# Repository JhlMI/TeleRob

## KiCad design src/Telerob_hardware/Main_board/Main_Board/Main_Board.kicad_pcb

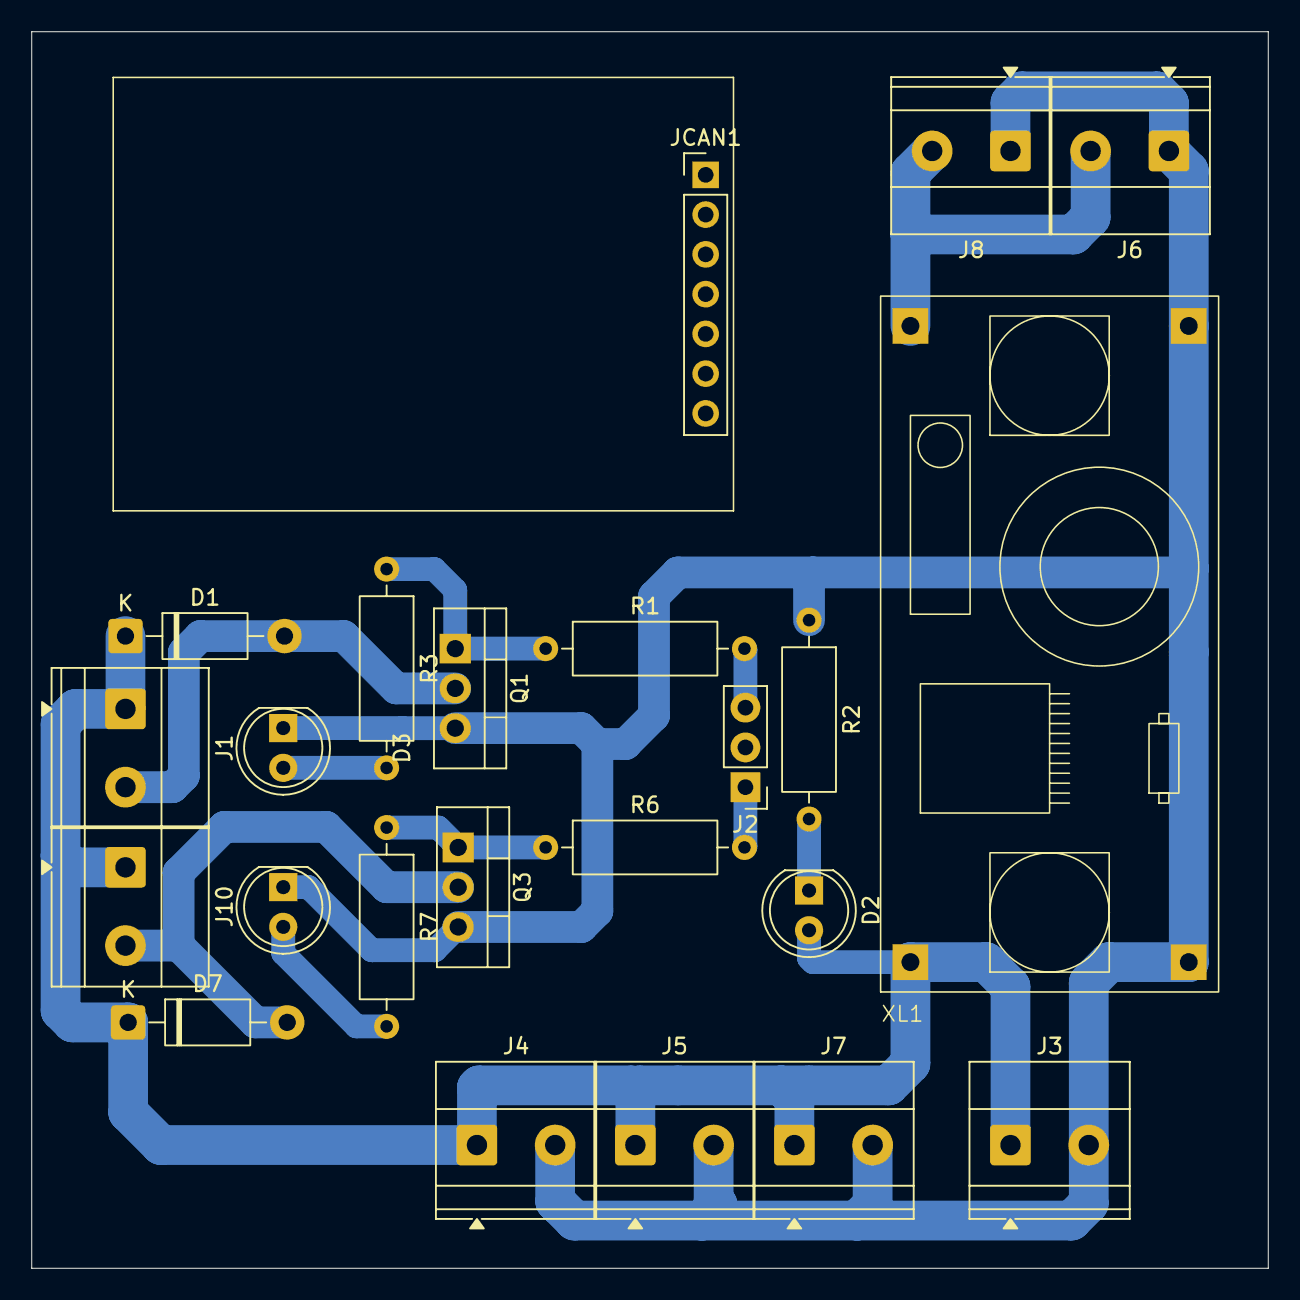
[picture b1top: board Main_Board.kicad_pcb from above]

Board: 2 copper layers, 79.0 x 79.0 mm, 23 parts (0 on the bottom side), 12 nets.

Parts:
D1, D7: 1N4007; D_DO-41_SOD81_P10.16mm_Horizontal
D2, D3, D6: LED; LED_D5.0mm
J1, J10: Mosfet; TerminalBlock_Phoenix_MKDS-1,5-2_1x02_P5.00mm_Horizontal
J2: Conn_01x03; PinHeader_1x03_P2.54mm_Vertical
J3, J6, J8: VIN; TerminalBlock_Phoenix_MKDS-1,5-2_1x02_P5.00mm_Horizontal
J4, J5, J7: VPico; TerminalBlock_Phoenix_MKDS-1,5-2_1x02_P5.00mm_Horizontal
JCAN1: CAN_BUS; PinHeader_1x07_P2.54mm_Vertical
Q1, Q3: IRLZ44N; TO-220-3_Vertical
R1, R2, R6: 1K; R_Axial_DIN0309_L9.0mm_D3.2mm_P12.70mm_Horizontal
R3, R7: 330; R_Axial_DIN0309_L9.0mm_D3.2mm_P12.70mm_Horizontal
XL1: XL4005; XL4005 footprint

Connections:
/5V_IN: J6.2, J8.2, XL1.2 (OUT+)
/12V: D1.1 (K), D2.2 (A), D7.1 (K), J1.1, J3.1, J4.1, J5.1, J7.1, J10.1, XL1.0 (IN+)
/GND: D3.1 (K), D6.1 (K), J3.2, J4.2, J5.2, J6.1, J7.2, J8.1, JCAN1.6, Q1.3 (S), Q3.3 (S), R2.1, XL1.1 (IN-), XL1.3 (OUT-)
/GP1: J2.3, R1.2
/GP3: J2.1, R6.2
unnamed: D1.2 (A), J1.2, Q1.2 (D)
unnamed: D2.1 (K), R2.2
unnamed: D3.2 (A), R3.2
unnamed: D6.2 (A), R7.2
unnamed: D7.2 (A), J10.2, Q3.2 (D)
unnamed: Q1.1 (G), R1.1, R3.1
unnamed: Q3.1 (G), R6.1, R7.1

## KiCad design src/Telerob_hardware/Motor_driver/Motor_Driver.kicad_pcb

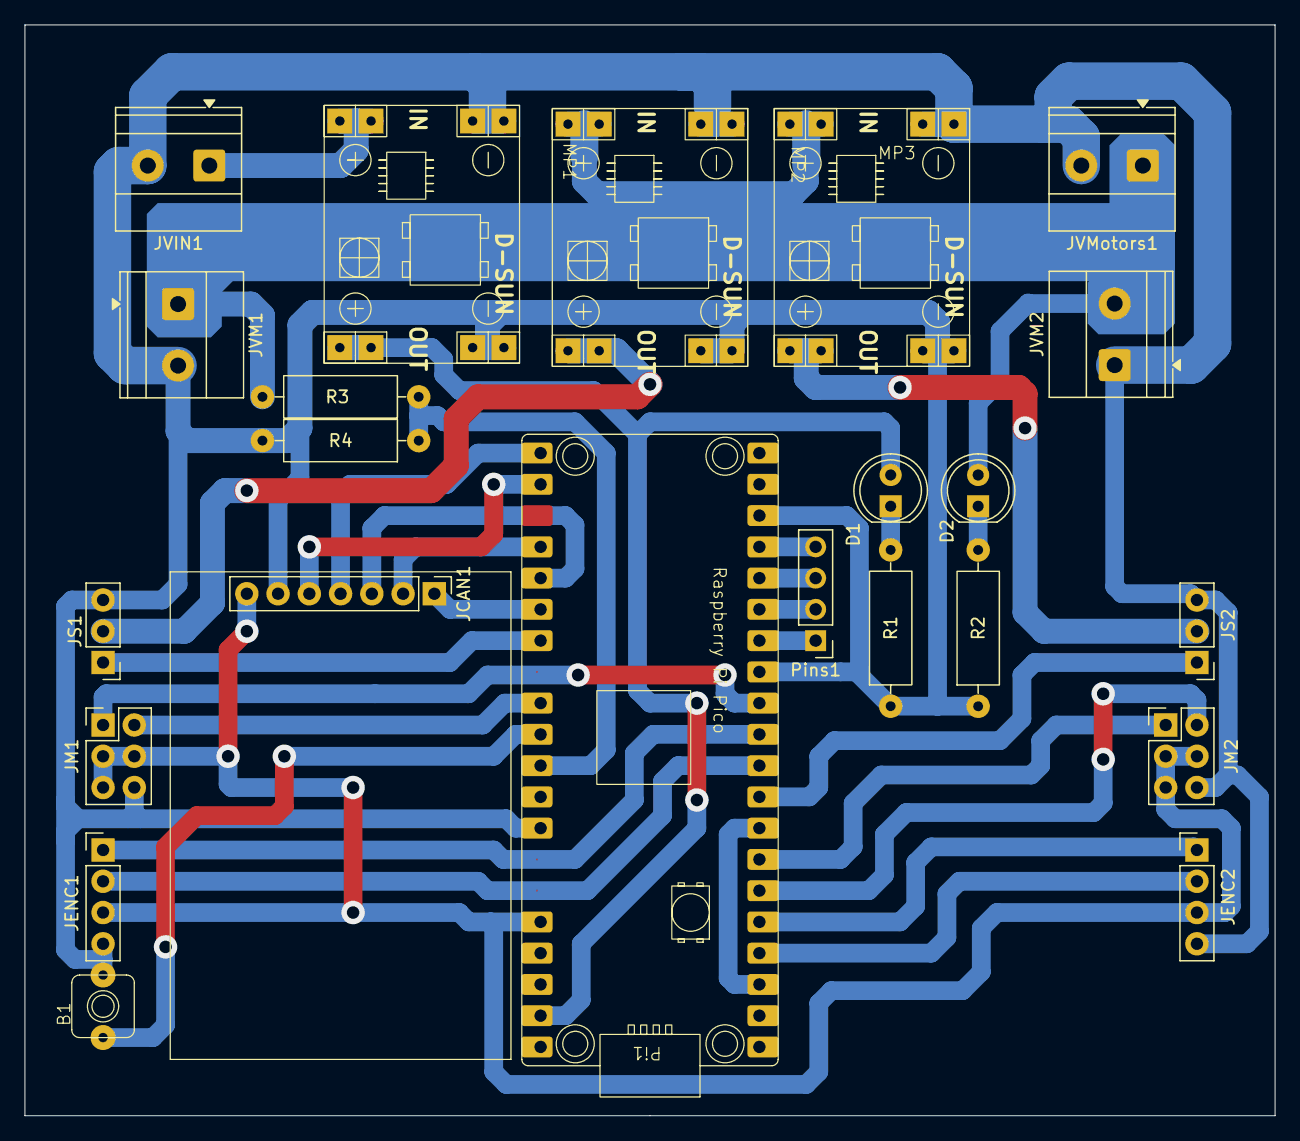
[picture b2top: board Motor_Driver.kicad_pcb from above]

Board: 2 copper layers, 101.6 x 88.6 mm, 23 parts (0 on the bottom side), 30 nets.

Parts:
B1: RST; BUTTON
D1, D2: LED; LED_D5.0mm
JCAN1: CAN_BUS; PinHeader_1x07_P2.54mm_Vertical
JENC1, JENC2: Enc1; PinHeader_1x04_P2.54mm_Vertical
JM1: Motor2; PinHeader_2x03_P2.54mm_Vertical
JM2: Motor1; PinHeader_2x03_P2.54mm_Vertical
JS1: Servo 1; PinHeader_1x03_P2.54mm_Vertical
JS2: Servo 2; PinHeader_1x03_P2.54mm_Vertical
JVIN1: VIN; TerminalBlock_Phoenix_MKDS-1,5-2_1x02_P5.00mm_Horizontal
JVM1: V_M1; TerminalBlock_Phoenix_MKDS-1,5-2_1x02_P5.00mm_Horizontal
JVM2: V_M2; TerminalBlock_Phoenix_MKDS-1,5-2_1x02_P5.00mm_Horizontal
JVMotors1: V_Motor; TerminalBlock_Phoenix_MKDS-1,5-2_1x02_P5.00mm_Horizontal
MP1, MP2, MP3: MP1584 STEP DOWN; MP1584
Pi1: Raspberry Pi Pico; RP_pico_footprint
Pins1: PinHeader_1x04_P2.54mm_Vertical
R1, R2: 1K; R_Axial_DIN0309_L9.0mm_D3.2mm_P12.70mm_Horizontal
R3: 22k; R_Axial_DIN0309_L9.0mm_D3.2mm_P12.70mm_Horizontal
R4: 6.8k; R_Axial_DIN0309_L9.0mm_D3.2mm_P12.70mm_Horizontal

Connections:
/3V3_O: JCAN1.7, JENC1.3, JENC2.3, JM1.3, JM1.4, JM1.5, JM2.3, JM2.4, JM2.5, Pi1.35 (3V3_O)
/5V_IN: D1.2 (A), MP1.3 (OUT+), Pi1.38 (VSYS)
/5V_S1: JS1.2, MP2.3 (OUT+)
/5V_S2: JS2.2, MP3.3 (OUT+)
/A_1: JENC1.2, Pi1.9 (GP7)
/A_2: JENC2.2, Pi1.3 (GP2)
/B_1: JENC1.1, Pi1.10 (GP8)
/B_2: JENC2.1, Pi1.4 (GP3)
/CS: JCAN1.5, Pi1.21 (GP17)
/GND: B1.1, JCAN1.6, JENC1.4, JENC2.4, JM1.6, JM2.6, JS1.3, JS2.3, JVIN1.2, JVM1.2, JVM2.1, JVMotors1.2, MP1.0 (IN-), MP1.2 (OUT-), MP2.0 (IN-), MP2.2 (OUT-), MP3.0 (IN-), MP3.2 (OUT-), Pi1.2 (GND), Pi1.7 (GND), Pi1.12 (GND), Pi1.17 (GND), Pi1.22 (GND), Pi1.27 (GND), Pi1.32 (GND), Pi1.37 (GND), R1.1, R2.1, R4.2
/GP4: JM2.2, Pi1.5 (GP4)
/GP5: JM2.1, Pi1.6 (GP5)
/GP6: JS2.1, Pi1.8 (GP6)
/GP9: JM1.1, Pi1.11 (GP9)
/GP10: Pi1.13 (GP10), Pins1.1
/GP11: Pi1.14 (GP11), Pins1.2
/GP12: Pi1.15 (GP12), Pins1.3
/GP13: Pi1.16 (GP13), Pins1.4
/GP21: JS1.1, Pi1.26 (GP21)
/GP22: JM1.2, Pi1.28 (GP22)
/INT: JCAN1.1, Pi1.25 (GP20)
/RUN: B1.0, Pi1.29 (RUN)
/SCK: JCAN1.2, Pi1.23 (GP18)
/SI: JCAN1.3, Pi1.24 (GP19)
/SO: JCAN1.4, Pi1.20 (GP16)
/VIN: JVIN1.1, MP1.1 (IN-)
/VM: D2.2 (A), JVM1.1, JVM2.2, JVMotors1.1, MP2.1 (IN-), MP3.1 (IN-), R3.2
/VML: Pi1.30 (GP26), R3.1, R4.1
unnamed: D1.1 (K), R1.2
unnamed: D2.1 (K), R2.2

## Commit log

2025-11-11 Files
2025-11-11 Files2
2025-11-11 Circ 2
2025-11-11 PCB_act
2025-11-15 Codes
